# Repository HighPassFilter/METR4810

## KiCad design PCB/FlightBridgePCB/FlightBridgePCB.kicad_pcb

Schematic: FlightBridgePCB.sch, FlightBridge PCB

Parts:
C1, C2: 22pF; C_0805_2012Metric_Pad1.18x1.45mm_HandSolder
C3, C4: 1uf; C_0805_2012Metric_Pad1.18x1.45mm_HandSolder
C5, C6, C7, C8: 1u; C_0805_2012Metric_Pad1.18x1.45mm_HandSolder
D1, D2, D3, D4, D5: LED; LED_0805_2012Metric_Castellated
J1: Raspberry_Pi_2_3; PinSocket_2x20_P2.54mm_Vertical
J2: AVR-ISP-6; PinHeader_2x03_P2.54mm_Vertical
J3: Conn_01x03; PinHeader_1x03_P2.54mm_Horizontal
J4: Conn_01x04; PinHeader_1x04_P2.54mm_Horizontal
J5: Conn_01x03; ELECTRICAL_Connection
Q1: IRF3205; TO-220-3_Vertical
Q2: BC849; SOT-23
R1: 1K; R_0805_2012Metric_Pad1.20x1.40mm_HandSolder
R2, R3, R4, R5, R6: 300; R_0805_2012Metric_Pad1.20x1.40mm_HandSolder
R9: 100k; R_0805_2012Metric_Pad1.20x1.40mm_HandSolder
R10: 1k; R_0805_2012Metric_Pad1.20x1.40mm_HandSolder
U1: ATmega128A-AU; TQFP-64_14x14mm_P0.8mm
U2: MCP1700-3302E_TO92; TO-92_Inline
Y1: Crystal; Crystal_SMD_HC49-SD

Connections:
+3V3: C4.1, C7.1, C8.1, J2.2 (VCC), J4.1, R1.1, R5.1, U1.21 (VCC), U1.52 (VCC), U1.64 (AVCC), U2.3
+5V: C5.1, C6.1, J1.2 (5V), J1.4 (5V), J3.1, R6.1
A: R2.1, U1.49 (PA2)
ABORT: J1.15 (GPIO22), U1.35 (PC0)
GND: C1.2, C2.1, C3.2, C4.2, C5.2, C6.2, C7.2, C8.2, D1.1 (K), D2.1 (K), D3.1 (K), D4.1 (K), D5.1 (K), J2.6 (GND), J4.2, J5.2, Q1.3 (S), Q2.2 (E), U1.22 (GND), U1.53 (GND), U1.63 (GND), U2.1
GND1: J1.6 (GND), J1.9 (GND), J1.14 (GND), J1.20 (GND), J1.25 (GND), J1.30 (GND), J1.34 (GND), J1.39 (GND), J3.2, J5.1, Q1.2 (D)
MISO: J2.1 (MISO), U1.3 (PE1)
MOSI: J1.8 (GPIO14/TXD), J2.4 (MOSI), J3.3, U1.2 (PE0)
N: R4.1, U1.47 (PA4)
unnamed: C1.1, U1.24 (XTAL1), Y1.1
unnamed: C2.2, U1.23 (XTAL2), Y1.2
unnamed: D1.2 (A), R2.2
unnamed: D2.2 (A), R3.2
unnamed: D3.2 (A), R4.2
unnamed: D4.2 (A), R5.2
unnamed: D5.2 (A), R6.2
unnamed: Q1.1 (G), Q2.3 (C), R9.2
unnamed: Q2.1 (B), R10.1
R: R3.1, U1.48 (PA3)
SCK: J2.3 (SCK), U1.11 (PB1)
SCL: J1.5 (SCL/GPIO3), J4.4
SDA: J1.3 (SDA/GPIO2), J4.3
SUPERVISOR_RESET: J1.16 (GPIO23), U1.36 (PC1)
UART_TELEM_PI: J1.10 (GPIO15/RXD)
Vin: C3.1, J5.3, R9.1, U2.2
~POWER_EN~: R10.2, U1.46 (PA5)
~RST~: J2.5 (~RST), R1.2, U1.20 (~RESET)

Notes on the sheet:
To/from Raspberry Pi
Rad-hard Supervisor IC
To/From Flight Controller
Indicator LEDs
3.3V Regulator
ATmega ISP Header
Power Switching Circuit
Pi I2C breakout

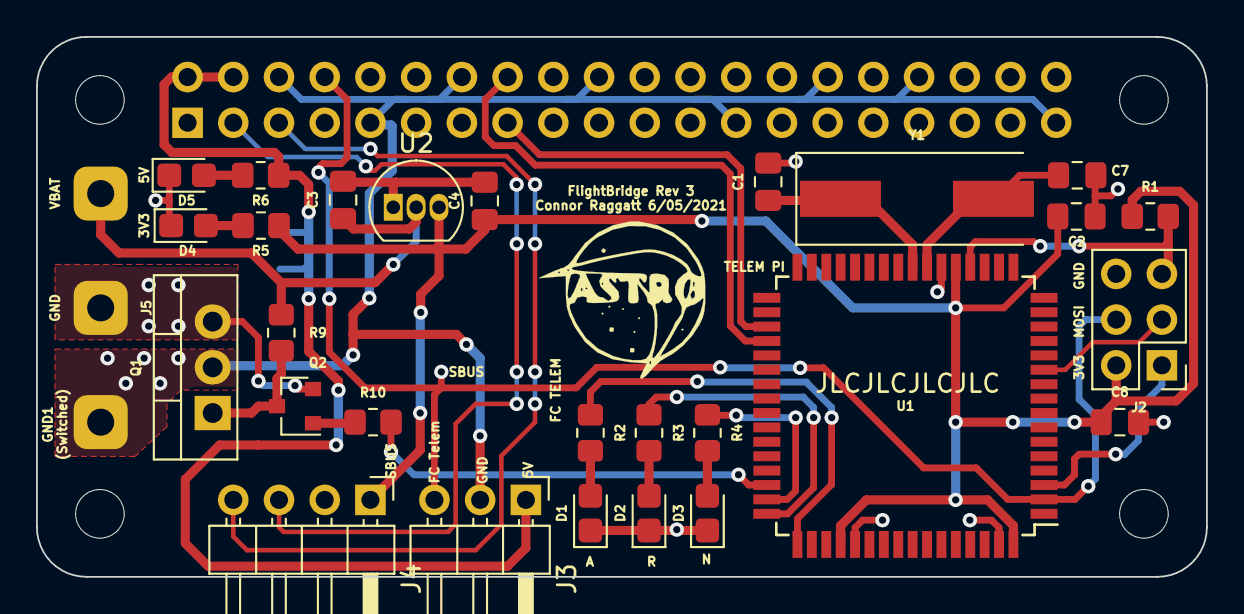
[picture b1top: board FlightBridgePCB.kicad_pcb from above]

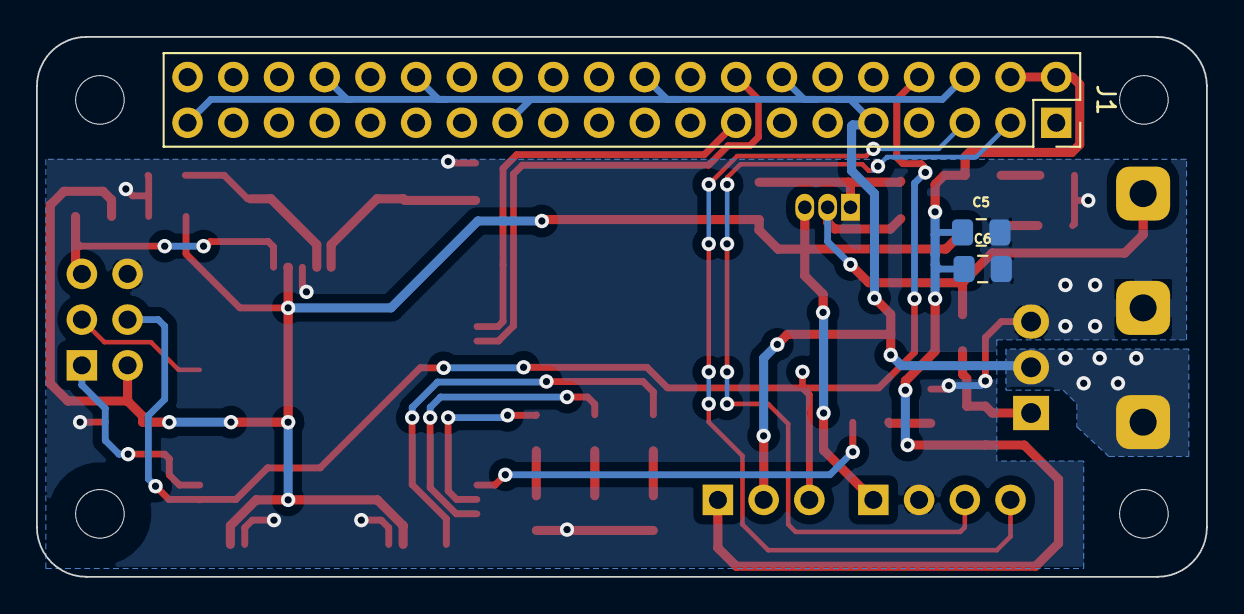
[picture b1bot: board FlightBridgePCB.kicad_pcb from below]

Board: 2 copper layers, 65.0 x 30.0 mm, 31 parts (3 on the bottom side), 26 nets.

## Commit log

2021-03-08 Addition of telemetry script
2021-03-08 Addition of client and server scripts
2021-03-08 test push
2021-03-10 Socket example using TCP packet stream
2021-03-10 Update client script
2021-03-12 Addition of WiFi library
2021-03-13 Debug WiFi class
2021-03-13 Addition of Robot class
2021-03-13 Work on closing connections + shutdown function
2021-03-13 Changes to shutdown features
2021-03-13 Changes made to data formatting functions
2021-03-13 Fixing packet sending
2021-03-13 Fixing receive data
2021-03-13 Fixed swapped functions for send and receive
2021-03-13 Fixed inifinite data packet sending
2021-03-13 Syntax change
2021-03-13 Fixed bug of no data return
2021-03-13 Worked on robot commands
2021-03-13 Fix thread termination
2021-03-13 Addition of robot commands
2021-03-13 Added Folder for embedded Code
2021-03-13 Addition of commands to ground station
2021-03-14 Added first sample project to prove workflow
2021-03-14 README.md
2021-03-14 removing unneeded files
2021-03-14 Added Serial Functionality to the program
2021-03-20 Code for sending data to groundstation
2021-03-20 bug fix
2021-03-20 Inbuilt user interface in thread
2021-03-20 minor change
2021-03-20 package data changes
2021-03-21 Addition of simple communication protocol
2021-03-21 Update communication protocol
2021-03-21 Solved data fragmentation
2021-03-21 Completed code for sensor data transfers
2021-03-21 mini update
2021-03-22 partial system implementation
2021-03-22 saved work
2021-03-22 Serial Driver begining functionality
2021-03-24 Real-time graph plotting completed
2021-03-24 Implemented sensor data storage
2021-03-29 Serial for PI Telemetry
2021-03-29 Minor fixes for serial code
2021-03-30 Added PCB to Git
2021-03-31 SBUS frist commit
2021-03-31 SBUS change 1
2021-03-31 SBUS change 2
2021-03-31 SBUS change 3
2021-03-31 SBUS change 4
2021-03-31 Change 5
2021-03-31 Adjust column labelling for ground station data storage
2021-03-31 Adjust agent threads to not running indefinitely
2021-03-31 SBUS 6
2021-04-01 Pyserial Fix for SBUS
2021-04-01 SBUS attempts
2021-04-01 Fix shut down feature of state machine
2021-04-01 unknown
2021-04-01 same
2021-04-01 More SBUS testing
2021-04-01 Update state machine architecture
2021-04-01 Fix sender indefinite queue get action
2021-04-01 Fixed shutdown
2021-04-01 Implemented client wait for server connection + feedack
2021-04-01 Mock reset command
2021-04-02 Code that works for command line reset
2021-04-04 PCB Update
2021-04-06 main pi ccode
2021-04-06 Servo code
2021-04-06 Adding vision code to repo
2021-04-06 April tag test code
2021-04-06 Added connors code
2021-04-12 First Full PCB
2021-04-12 PCB Updates
2021-04-12 Added reuse address feature
2021-04-18 First PCB to be Built
2021-04-23 Addition of telemetry class
2021-04-23 Addition of extra methods to Telemery class
2021-04-23 Modified data packing for sending
2021-04-23 Modified stateDescent to obtain and send real data
2021-04-23 Debugging Telemetry class
2021-04-23 Debugging robot class
2021-04-23 Addition of error checking to sensor data
2021-04-23 Minor bug fix
2021-04-23 Fix string building in data packing function
2021-04-23 Remove unecessary prints
2021-04-23 Fixing the rate of sensor data transfer
2021-04-29 Add temperature + pressure API to telemetry class
2021-04-29 bug fix for telemetry
2021-04-29 Fix address of BMP280
2021-04-29 Update GUI to include all necessary plots
2021-04-29 Addition of exceptions to handle sensor errors
2021-04-30 Added ability to store linear acceleration data
2021-04-30 Removed integration with FC
2021-04-30 Removed integration from FC
2021-04-30 More debugging
2021-04-30 Corrected sensor storage in robot
2021-04-30 Change IMU mode to raise data output
2021-05-06 New PCB
2021-05-09 Test of SBUS
2021-05-09 added new vision code
2021-05-09 added new vision code2
2021-05-09 vision pt 3
2021-05-10 test world frame orientation
2021-05-10 Changed sensor storage method
2021-05-10 Fixed bug
2021-05-10 Fix matrix multiplication
2021-05-10 Fixed error on None
2021-05-10 Fix none ori errors
2021-05-10 fix wrong data format for lin_acc
2021-05-10 record flat orientation
2021-05-10 Addition of experiment mode
2021-05-10 Clean robot code
2021-05-11 Test code for abort mode
2021-05-12 Threading for SBUS
2021-05-12 SBUS threading test code
2021-05-12 more complete implementation of SBUS thread
2021-05-12 inclusion of timer for SBUS thread
2021-05-12 test
2021-05-12 full implementation of SBUS threads
2021-05-12 Update SBUS integration into robot state machine
2021-05-12 Integrate FC shutdown
2021-05-12 abort mode settings
2021-05-12 Abort settings update
2021-05-12 Throttle set to zero initially
2021-05-12 Addition of servo release code
2021-05-12 Change of drone arming sequence
2021-05-12 servo position change
2021-05-13 Added colour refined code
2021-05-13 Code now returns offset from center
2021-05-13 Establish setup state
2021-05-13 Added arm and updated decent state
2021-05-13 Update to state machine
2021-05-13 update state machine in ground stattion
2021-05-13 State machine update
2021-05-13 update channel numbers
2021-05-13 Working ATMega Code
2021-05-13 Start form different state
2021-05-13 lockin debug
2021-05-13 added ex state machine
2021-05-13 Updated state machine architecture
2021-05-14 Disable throttle up
2021-05-14 Thread camera module
2021-05-15 optimizing computer vision code
2021-05-16 Changed to new state machine
2021-05-16 slowed motor down
2021-05-16 added keypress stuff
2021-05-18 Camera test code for connor
2021-05-18 More camera tests
2021-05-18 Tests
2021-05-18 statemachine tests
2021-05-18 More Test
2021-05-18 Updated ExampleStateMachine.py
2021-05-20 Disable listener in Server
2021-05-20 Implement queue timeouts
2021-05-20 Trying different vision code
2021-05-20 saved stuff
2021-05-20 added sensor measuring
2021-05-20 fixing sensor stuff
2021-05-20 updated control
2021-05-20 updated centre position
2021-05-23 Code clean up
2021-05-23 Code clean up round 2
2021-05-23 LifoQueue change
2021-05-23 Move vision code to robot
2021-05-23 move vision to computer
2021-05-23 removed multithreading from code
2021-05-23 Change GUI to process
2021-05-23 debug GUI
2021-05-23 Remove listener shutdown
2021-05-23 Correct for world coordinates
2021-05-23 Revert "Correct for world coordinates"
    This reverts commit 9dc886c41273ad5b7c362f9e4fbd1c0d7e86de5c.
